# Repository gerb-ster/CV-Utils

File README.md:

# CV-Utils

A simple CV utilities module

## Status: Work in Progress

- done: first schematic & board design
- todo: breadboard and test
- todo: design frontpanel
- todo: order PCB and build prototype

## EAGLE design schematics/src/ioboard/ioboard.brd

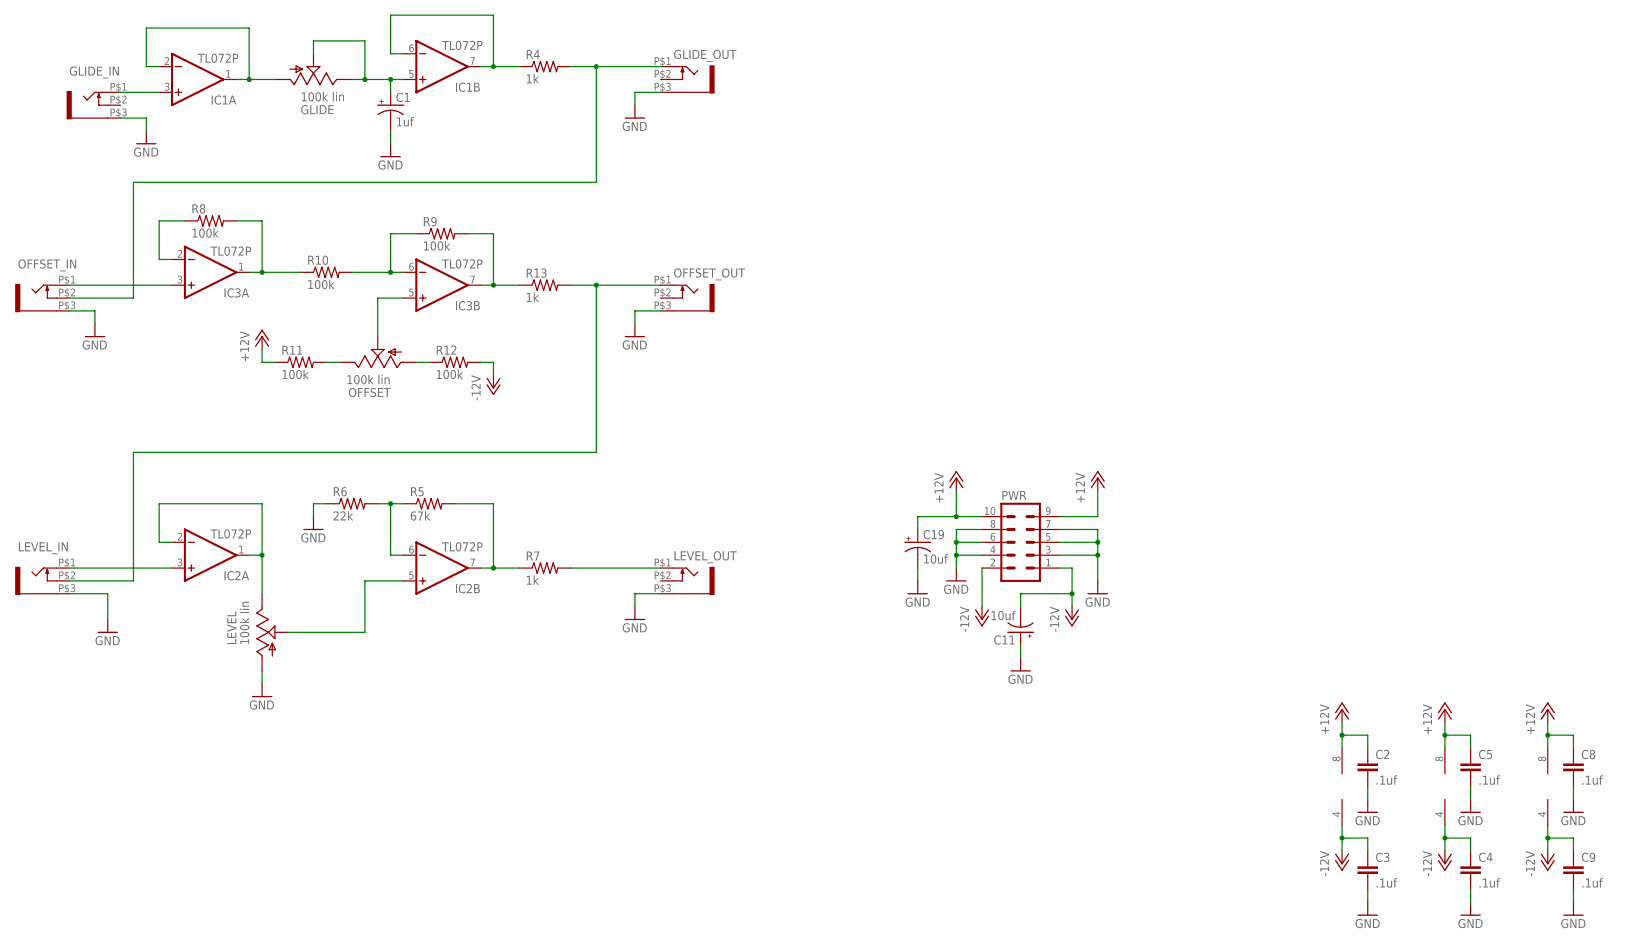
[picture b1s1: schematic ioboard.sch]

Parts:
C1: 1uf; E2,5-6
C2, C3, C4, C5, C8, C9: .1uf; C050-024X044
C11, C19: 10uf; E2,5-5
GLIDE: 100k lin; EVUF
GLIDE_IN: WQP-PJ301M-12_JACK
GLIDE_OUT: WQP-PJ301M-12_JACK
IC1, IC2, IC3: TL072P; DIL08
LEVEL: 100k lin; EVUF
LEVEL_IN: WQP-PJ301M-12_JACK
LEVEL_OUT: WQP-PJ301M-12_JACK
OFFSET: 100k lin; EVUF
OFFSET_IN: WQP-PJ301M-12_JACK
OFFSET_OUT: WQP-PJ301M-12_JACK
PWR: ML10
R4, R7, R13: 1k; 0204/7
R5: 67k; 0204/7
R6: 22k; 0204/7
R8, R9, R10, R11, R12: 100k; 0204/7

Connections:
+12V: C2.1, C5.1, C8.1, C19.+, IC1.8 (V+), IC2.8 (V+), IC3.8 (V+), PWR.9, PWR.10, R11.1
-12V: C3.1, C4.1, C9.1, C11.-, IC1.4 (V-), IC2.4 (V-), IC3.4 (V-), PWR.1, PWR.2, R12.2
GND: C1.-, C2.2, C3.2, C4.2, C5.2, C8.2, C9.2, C11.+, C19.-, GLIDE_IN.P$3 (1), GLIDE_OUT.P$3 (1), LEVEL.1 (A), LEVEL_IN.P$3 (1), LEVEL_OUT.P$3 (1), OFFSET_IN.P$3 (1), OFFSET_OUT.P$3 (1), PWR.3, PWR.4, PWR.5, PWR.6, PWR.7, PWR.8, R6.1
IO_LEVEL_W: IC2.5 (+IN), LEVEL.2 (S)
IO_OFFSET_IN: IC3.3 (+IN), OFFSET_IN.P$1 (2)
IO_OFFSET_OUT: LEVEL_IN.P$2 (3), OFFSET_OUT.P$1 (2), R13.2
IO_SLIDE_A: GLIDE.1 (A), IC1.1 (OUT), IC1.2 (-IN)
IO_SLIDE_B: C1.+, GLIDE.2 (S), GLIDE.3 (E), IC1.5 (+IN)
IO_SLIDE_IN: GLIDE_IN.P$1 (2), IC1.3 (+IN)
M_LEVEL_A: IC2.1 (OUT), IC2.2 (-IN), LEVEL.3 (E)
M_LEVEL_IN: IC2.3 (+IN), LEVEL_IN.P$1 (2)
M_LEVEL_OUT: LEVEL_OUT.P$1 (2), R7.2
M_OFFSET: IC3.5 (+IN), OFFSET.2 (S)
M_SLIDE_OUT: GLIDE_OUT.P$1 (2), OFFSET_IN.P$2 (3), R4.2
unnamed: IC1.6 (-IN), IC1.7 (OUT), R4.1
unnamed: IC2.6 (-IN), R5.1, R6.2
unnamed: IC2.7 (OUT), R5.2, R7.1
unnamed: IC3.6 (-IN), R9.1, R10.2
unnamed: IC3.1 (OUT), R8.2, R10.1
unnamed: IC3.2 (-IN), R8.1
unnamed: IC3.7 (OUT), R9.2, R13.1
unnamed: OFFSET.1 (A), R12.1
unnamed: OFFSET.3 (E), R11.2

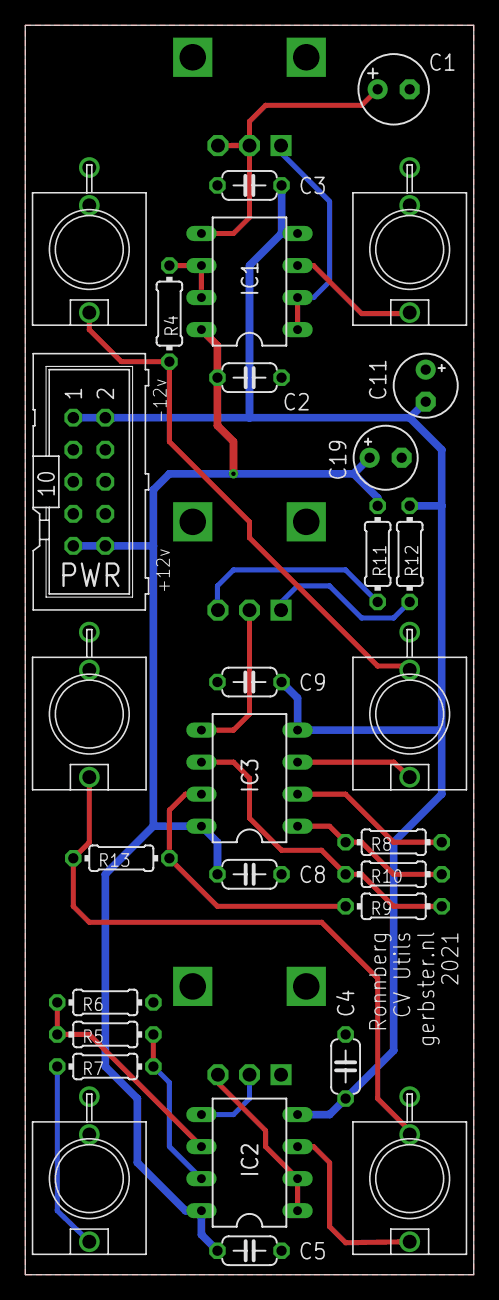
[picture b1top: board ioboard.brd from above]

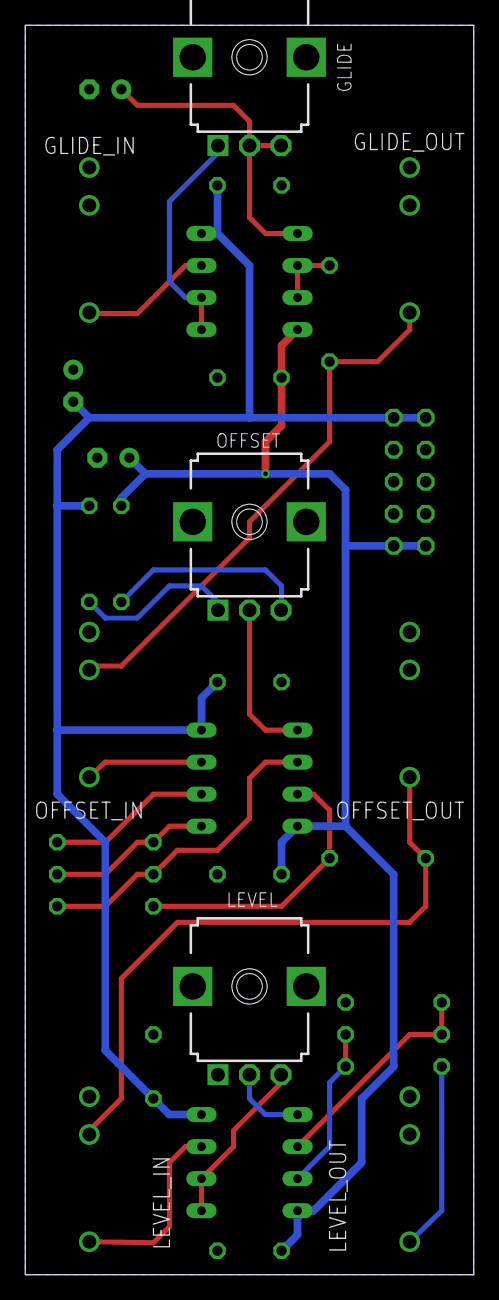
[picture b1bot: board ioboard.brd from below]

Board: 2 copper layers, 35.6 x 99.1 mm, 32 parts (3 on the bottom side), 23 nets.

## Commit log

2021-04-29 board and schematic setup
2021-05-01 done
2021-05-01 no message
2021-05-06 changed schematic
2021-05-06 removed some unwanted files
2021-05-07 Added files & structere
2021-05-10 Added Status
2021-05-11 Added Status & Images
2021-05-12 Added Faceplates
2021-06-15 Updated Schematics, Fixed Power Socket orientation
2021-08-06 Updated some schematics and docs
2021-08-10 Fixed some bugs and updated documentation
2022-04-20 Some updates & bugfixes
2022-04-22 Fixed schematics & descriptions
2022-05-17 Updated Firmware
2022-05-18 Updated Faceplates
2022-05-18 Fixed issues
2022-05-21 Fixed schematics
2022-05-28 General updates
2022-06-13 Faceplates & Bugfixes
